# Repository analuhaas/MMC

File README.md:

# MMC

This repository contains the codes, simulation models and documentation of the open-source Modular Multilevel Converter (MMC) developed in the **CARROTS** project with [OwnTech](https://www.owntech.io/) suite.

The development of the project is followed in the [repository issues](../../issues), where you can find its latest updates.

## The CARROTS project

### Context

The energy transition is changing the electrical grid. More and more generation is connected locally to the medium-voltage (MV) grid, pushed by policies such as the French law that requires photovoltaic panels over parking lots larger than 1500 m². DC grids, and MVDC grids in particular, are a promising way to connect these sources and loads. Their main challenge is that they need **non-standard power converters**, which are expensive to design for each application.

The **Modular Multilevel Converter (MMC)** is a good candidate: it is standard, modular and scalable, since it is made of identical modules connected in series. However, its control and communication are complex. They usually rely on a centralized master controller that must measure and command every module. This controller is expensive and limits the use of MMCs in MV applications.

CARROTS proposes to replace the master controller by a local controller (LC) in each module, which communicate with each other:

*MMC with (a) a centralized control and data architecture and (b) a decentralized control and data architecture (expected outcome of CARROTS).*

### Objective

CARROTS aims to develop a **generic, masterless and open-source MMC**:

- **Generic**: the proposed converter will be based on standard blocks and must be adaptable to different voltage and power levels.
- **Masterless**: the control is distributed between the modules, without a central controller.
- **Open-source**: the hardware and software are based on the OwnTech TWIST and SPIN boards, and are shared openly.

To reach this objective, the project addresses three scientific barriers, each one handled by a work package (WP), plus an integration WP:

| Work package | Barrier | Topics |
|---|---|---|
| **WP1 – Power** | Sizing, modeling and testing the converter | Sizing of generic converters, frugal digital twins, prototype test protocols |
| **WP2 – Control** | Controlling the MMC without a master | Cooperative distributed control |
| **WP3 – Data** | Exchanging data between the modules | Peer-to-peer real-time communication |
| **WP4 – Integration** | Building and testing the prototypes | Integration of power, control and data in the MMC prototypes |

The control is decentralized in two steps:

- **MMC V1**: a single arm of 5 OwnTech modules, where the control and data are decentralized inside the arm (intra-arm). The master controller is replaced by local controllers that collaborate.

*MMC V1: intra-arm control and data decentralization.*

- **MMC V2**: a three-phase MMC with 6 arms, where the control and data are also decentralized between the arms (cross-arm).

*MMC V2: cross-arm control and data decentralization.*

### Contributors

4 laboratories and OwnTech contributes to the development of this open-source MMC:
- GeePs
    * Ana Luiza HAAS BEZERRA (PhD student WP1)
    * Noemi LANCIOTTI
    * Alexandre BACH
    * Loïc QUÉVAL
- G2ELab
    * Zaid JABBAR (PhD student WP2)
    * Adrien CORNE
    * David FREY
- LAAS-CNRS
    * Ayoub FARAH (PhD student WP3)
    * Clément FOUCHER
    * Luiz VILLA
- L2EP
    * François GRUSON
- [OwnTech Technologies](https://www.owntech.io/)
    * Jean ALINEI (Engineer WP4)

The CARROTS project is funded by the French National Research Agency (ANR) under the grant ANR-24-CE05-0920-01. The coordinator is Loïc Quéval.

## Repository content

```
MMC_OwnTech_Foundation
└─ MMC_codes                  Firmware of the MMC prototypes (PlatformIO projects)
|  └─ Educational prototype   Calibration, module tests, stack (with/without CVB) and phase tests
|  └─ Control logic           Standalone test of the NLM + sorting + CVB logic
|  └─ JCGE                    Codes of the 3rd OwnTech hackathon (JCGE)
|  └─ Other                   Blinky MMC stack and ScopeMimicry plot scripts
└─ MMC_documentation          Tutorials
|  └─ Getting started         Git/VS Code/PlatformIO and KiCad configuration
|  └─ Prototype tutorials     Step-by-step tutorials to build and test the prototype
|  └─ Others                  CVB logic and blinky MMC tutorials
|  └─ figures                 Figures used in the tutorials
└─ MMC_models                 MATLAB/Simulink models of the prototypes
|  └─ Educational prototype   Module, stack and phase simulations
|  └─ JCGE                    Models of the 3rd OwnTech hackathon (JCGE)
└─ schematics                 draw.io sources of the figures (hardware and communication)
└─>LICENSE.txt
└─>README.md
```

### MMC_codes

Each code folder is a PlatformIO project with its own README that explains the code and how to use it.

| Code | Description |
|---|---|
| [module_calibration](MMC_codes/Educational%20prototype/module_calibration/README.md) | Manual calibration of the TWIST sensors |
| [module_calibration_automated](MMC_codes/Educational%20prototype/module_calibration_automated/README.md) | Automated calibration of the TWIST sensors |
| [module_test_sequences](MMC_codes/Educational%20prototype/module_test_sequences/README.md) | Low-frequency (LF) and high-frequency (HF) test sequences of a single module |
| [stack_no_CVB](MMC_codes/Educational%20prototype/stack_no_CVB/README.md) | Stack of 5 modules with NLM and without capacitor voltage balancing |
| [stack_with_cvb](MMC_codes/Educational%20prototype/stack_with_cvb/README.md) | Stack of 5 modules with NLM and CVB |
| [phase_NLM_with_cvb](MMC_codes/Educational%20prototype/phase_NLM_with_cvb/README.md) | MMC phase of 10 modules (two stacks) with NLM and CVB |
| [Control logic](MMC_codes/Control%20logic/README.md) | NLM, sorting and CVB logic tested without power |
| [blinky_mmc_stack](MMC_codes/Other/blinky_mmc_stack/README.md) | First communication test between the boards of a stack |
| [scopemimicry_plot](MMC_codes/Other/scopemimicry_plot/README.md) | MATLAB/Python scripts to plot the ScopeMimicry data |

### MMC_documentation

The tutorials guide the user from the configuration of the computer to the test of an MMC phase:

1. [VS Code and Git configuration](MMC_documentation/Getting%20started/Vscode_for_OwnTech_configuration.md) and [KiCad configuration](MMC_documentation/Getting%20started/owntech_kicad_tutorial.md)
2. [Hardware modifications of the TWIST board for the MMC](MMC_documentation/Prototype%20tutorials/twist_modifications_MMC_tutorial.md), [module capacitor board](MMC_documentation/Prototype%20tutorials/KiCad_module_capacitor) and [rack](MMC_documentation/Prototype%20tutorials/Rack_project)
3. [Module calibration](MMC_documentation/Prototype%20tutorials/module_calibration_tutorial.md) (or its [automated version](MMC_documentation/Prototype%20tutorials/module_calibration_automated_tutorial.md))
4. [Module test sequences](MMC_documentation/Prototype%20tutorials/module_test_sequences_tutorial.md)
5. [Stack test with NLM without CVB](MMC_documentation/Prototype%20tutorials/stack_NLM_noCVB_test_tutorial.md) and [with CVB](MMC_documentation/Prototype%20tutorials/stack_NLM_CVB_test_tutorial.md)
6. [Phase test with NLM and CVB](MMC_documentation/Prototype%20tutorials/phase_NLM_CVB_test_tutorial.md)

Other tutorials: [plotting ScopeMimicry data](MMC_documentation/Prototype%20tutorials/scopemimicry_plot_tutorial.md), [CVB logic](MMC_documentation/Others/CVB_logic_tutorial.md) and [blinky MMC stack](MMC_documentation/Others/blinky_mmc_stack_tutorial.md).

### MMC_models

MATLAB/Simulink models of the TWIST-based prototype, which can be compared with the experimental results:

- [Module](MMC_models/Educational%20prototype/Module/README.md): low-frequency test of a single module.
- [Stack](MMC_models/Educational%20prototype/Stack/README.md): stack of 5 modules with NLM and CVB.
- [Phase](MMC_models/Educational%20prototype/Phase/README.md): MMC phase with centralized NLM, decentralized NLM and PWM with consensus.

The stack and phase models couple hardware, communication and control blocks, which can be adapted to the application.

## Getting started

1. Install [Git](https://git-scm.com/) and [VS Code with PlatformIO](https://platformio.org/install/ide?install=vscode), as explained in the [getting started tutorial](MMC_documentation/Getting%20started/Vscode_for_OwnTech_configuration.md).
2. Load the MMC codes in the project: in `platformio.ini`, replace the `owntech_examples` link with `https://github.com/analuhaas/examples.git`, then click on the PlatformIO icon and select the code under `Examples Twist` in the Project Tasks tab. The `main.cpp` files in [MMC_codes](MMC_codes) are the same codes, for reference.
3. Follow the tutorial of the code in [MMC_documentation](MMC_documentation).

For more information about the OwnTech Power API, see the [OwnTech documentation](https://docs.owntech.org/).

## License

See [LICENSE.txt](LICENSE.txt).

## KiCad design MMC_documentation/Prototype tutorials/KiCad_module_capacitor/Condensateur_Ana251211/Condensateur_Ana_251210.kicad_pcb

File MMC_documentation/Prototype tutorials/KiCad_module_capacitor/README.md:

# Module capacitor extension board (KiCad project)

This KiCad project is an extension board used to increase the capacitance of an MMC module built with a TWIST board. It is connected in parallel to the module capacitor $C_{High}$ through the VHigh and GND terminals of the TWIST board.

The TWIST high-side capacitor $C_{High}$ (188.6 µF) is used as the module capacitor, but it is too small to sustain the energy needed for operation at 50 Hz: the capacitors charge and discharge too fast, which increases the voltage ripple and deforms the stack voltage. The reasons and the impact on the stack behavior are explained in the [TWIST modifications for MMC tutorial](../twist_modifications_MMC_tutorial.md).

## Board description

The board holds up to 4 electrolytic capacitors in parallel (C1 to C4) and a 2-pole terminal block (J1) to connect it to the module:

| Reference | Component | Quantity | Supplier reference |
|---|---|---|---|
| C1, C2, C3, C4 | Electrolytic capacitor 560 µF, 250 V, CHEMI-CON LXS series (`ELXS251VSN561MR25S`) | 4 | RS Components 914-3692 |
| J1 | 2-pole PCB terminal block (`1715721`) | 1 | [RS Components 193-0564](https://fr.rs-online.com/web/p/embases-circuits-imprimes/1930564) |

- **Board size:** 157.48 mm × 35.56 mm.
- **Terminals:** J1 has a V+ pin, to connect to **VHigh**, and a V− pin, to connect to **GND** of the TWIST board.
- **Mounting:** 4 holes of 3 mm at the corners, used to stack several extension boards with spacers.

With the 4 capacitors mounted, the board adds $4 \times 560 = 2240$ µF in parallel to $C_{High}$, giving about 2430 µF per module.

!!! warning Polarity and voltage
    Respect the polarity of the electrolytic capacitors and of the connection (V+ to VHigh, V− to GND). Make sure the capacitor voltage rating is above the maximum module capacitor voltage of your test.

If you use other capacitors, adapt the size and spacing of the capacitor holes (footprint `CAPPRD1000W180D3050H2750`) on the PCB.

## Usage in the prototype

One extension board is connected to each module of the stack, using cables between its terminal block and the VHigh and GND terminals of the module. The boards of a stack can be piled up, forming a tower beside the stack:

## Project files

The project is in the [Condensateur_Ana251211](Condensateur_Ana251211) folder:

| File / folder | Content |
|---|---|
| `Condensateur_Ana_251210.kicad_pro` | KiCad project (open this file with KiCad) |
| `Condensateur_Ana_251210.kicad_sch` | Schematic |
| `Condensateur_Ana_251210.kicad_pcb` | PCB layout |
| `Symbole/`, `Footprint/` | Project symbol and footprint libraries (capacitor and terminal block) |
| `Composants/` | Downloaded component libraries and 3D models |

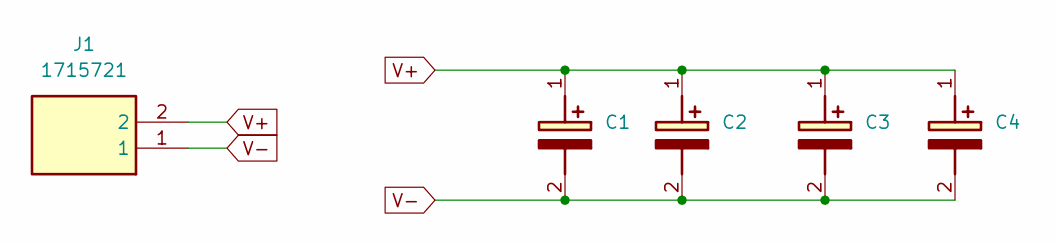
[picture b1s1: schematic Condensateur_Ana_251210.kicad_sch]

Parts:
C1, C2, C3, C4: ELXS251VSN561MR25S; CAPPRD1000W180D3050H2750; Mouser Part Number 661-ELXS251VSN561MR2
J1: 1715721; Mouser Part Number 651-1715721

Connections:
V+: C1.1 (+), C2.1 (+), C3.1 (+), C4.1 (+), J1.2
V-: C1.2 (-), C2.2 (-), C3.2 (-), C4.2 (-), J1.1

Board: 2 copper layers, 5 parts (0 on the bottom side), 2 nets, no tracks yet.

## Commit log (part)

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2026-02-19 Added all current module/stack/phase models on GitHub
2026-02-23 Update module_LF_test_tutorial.md with executing tutorial part
2026-02-23 Update module_LF_test_tutorial.md fixing format errors
2026-02-23 Added LF test tutorial file copy
2026-02-23 Update module_LF_test_tutorial.md LF only
2026-02-23 Added stack CVB tutorial copy
2026-02-23 Update stack_openloop_CVB_test_tutorial.md only cvb content
2026-02-23 Update stack_openloop_CVB_test_tutorial.md small mistake
2026-02-23 Create Vscode for OwnTech configuration
2026-02-23 Update module_HF_test_tutorial.md adding buttons images
2026-02-23 Update module_LF_test_tutorial.md adding buttons icons
2026-02-23 Update stack_openloop_CVB_test_tutorial.md adding buttons icons
2026-02-23 Update stack_openloop_noCVB_test_tutorial.md adding buttons icons
2026-02-23 Update Vscode for OwnTech configuration.md typing errors
2026-02-23 Update phase_openloop_CVB_test_tutorial.md with objectives and well defined sections
2026-02-25 Update phase_openloop_CVB_test_tutorial.md added circuits figures and simulation results with circulating current
2026-03-05 Update README_Simulink_MMC_Module_TWIST_model_LFtest.md with introduction
2026-03-05 Update module_LF_test_tutorial.md with table
2026-03-05 Update module_HF_test_tutorial.md with table
2026-03-05 Update README_Simulink_MMC_Module_TWIST_model_LFtest.md with simulink content
2026-03-05 Update README_Simulink_MMC_Module_TWIST_model_HFtest.md with simulink content
2026-03-05 Update README_Simulink_MMC_Module_TWIST_model_LFtest.md adding missing output plus removing unused variable
2026-03-05 Update README_Simulink_MMC_Stack_TWIST_model_CVBtest.md with simulink details
2026-03-05 Update README_Simulink_MMC_Stack_TWIST_model_dutycycleramp.md with Simulink details
2026-03-05 Update README_Simulink_MMC_Stack_TWIST_model_noCVBtest.md with Simulink details
2026-03-05 Update README_Simulink_MMC_Stack_TWIST_model_CVBmodifiedtest.md with simulink details
2026-03-05 Update README_Simulink_MMC_Stack_TWIST_model_CVBmodifiedtest.md CVB modified algorithm figure changed
2026-03-05 Update README_Simulink_MMC_Phase_TWIST_model_circuit1.md with simulink details
2026-03-05 Update README_Simulink_MMC_Phase_TWIST_model_circuit1.md with circuits photo
2026-03-05 Update README_Simulink_MMC_Phase_TWIST_model_circuit2.md with simulink details
2026-03-05 Update README_Simulink_MMC_Phase_TWIST_model_circuit3.md with simulink details
2026-03-05 Update README_Simulink_MMC_Phase_TWIST_model_circuit4.md with simulink details
2026-03-05 Update README_Simulink_MMC_Phase_TWIST_model_circuit1.md with expected results
2026-03-05 Update README_Simulink_MMC_Phase_TWIST_model_circuit2.md with expected results
2026-03-05 Update README_Simulink_MMC_Phase_TWIST_model_circuit3.md with expected results
2026-03-05 Update README_Simulink_MMC_Phase_TWIST_model_circuit4.md with expected results
2026-03-05 Update README_Simulink_MMC_Phase_TWIST_model_circuit2.md updates simulink circuit photo
2026-03-05 Update README_Simulink_MMC_Phase_TWIST_model_circuit3.md with simulink circuit photo
2026-03-05 Update README_Simulink_MMC_Phase_TWIST_model_circuit4.md with simulink circuit photo
2026-03-06 Update module_LF_test_tutorial.md with correction for minor errors
2026-03-06 Update module_HF_test_tutorial.md with correction for minor errors
2026-03-06 Update stack_openloop_CVB_test_tutorial.md correcting writing errors
2026-03-06 Update stack_openloop_noCVB_test_tutorial.md correcting minor errors on tutorial writing
2026-03-06 Adapted simulink files to README structure
2026-03-06 Update phase_openloop_CVB_test_tutorial.md with new images
2026-04-03 Creating subsystem for arm level, moving modulation block in control
2026-04-03 Creating monitoring subsystem, arm level subsystem, connect power level directly to control level
2026-04-03 Removing intermmediare block in TWIST subsystem, adding color rules for labels, input and output
2026-04-08 Use label color rule for each Twist subsystem
2026-04-08 adding name to wire and net
2026-04-28 update gitignore
2026-04-28 update schematic to implement hardware->communication->control structure
2026-05-11 Changed hardware block in simulink, making pwm, measurement, feeder and driver blocks and adding the electrical circuit to the hardware block such that inputs and outputs are clearer
2026-05-26 Modified phase tutorials markdown to add experimental results and fuses substitutions photos
2026-05-26 Added snippet of calibration to the markdown
2026-05-26 Added instructions to calibrate the board sensors
2026-05-26 Added figures to examplificate the fuses substitution
2026-05-26 Separated into modifications and calibration tutorials
2026-05-26 Added all images of circuit configurations
2026-05-31 Added results to phase tutorial and updated owntech kicad tutorial
2026-06-01 Added tutorial for calibration
2026-06-01 Substituted images for inside images only
2026-06-01 Substituted images of circuits
2026-06-01 Changed how the images are called on the markdown
2026-06-01 Changed how the images are called on the markdown again
2026-06-01 Changed how to put cone snippet
2026-06-01 Changed how to put cone snippet 2
2026-06-01 Changed how to put cone snippet 3
2026-06-01 Changed how to put cone snippet 4
2026-06-01 Added snippet of the boards IDs
2026-06-01 Changed requirements for phase tutorial
2026-06-15 Added MMC codes to repo
